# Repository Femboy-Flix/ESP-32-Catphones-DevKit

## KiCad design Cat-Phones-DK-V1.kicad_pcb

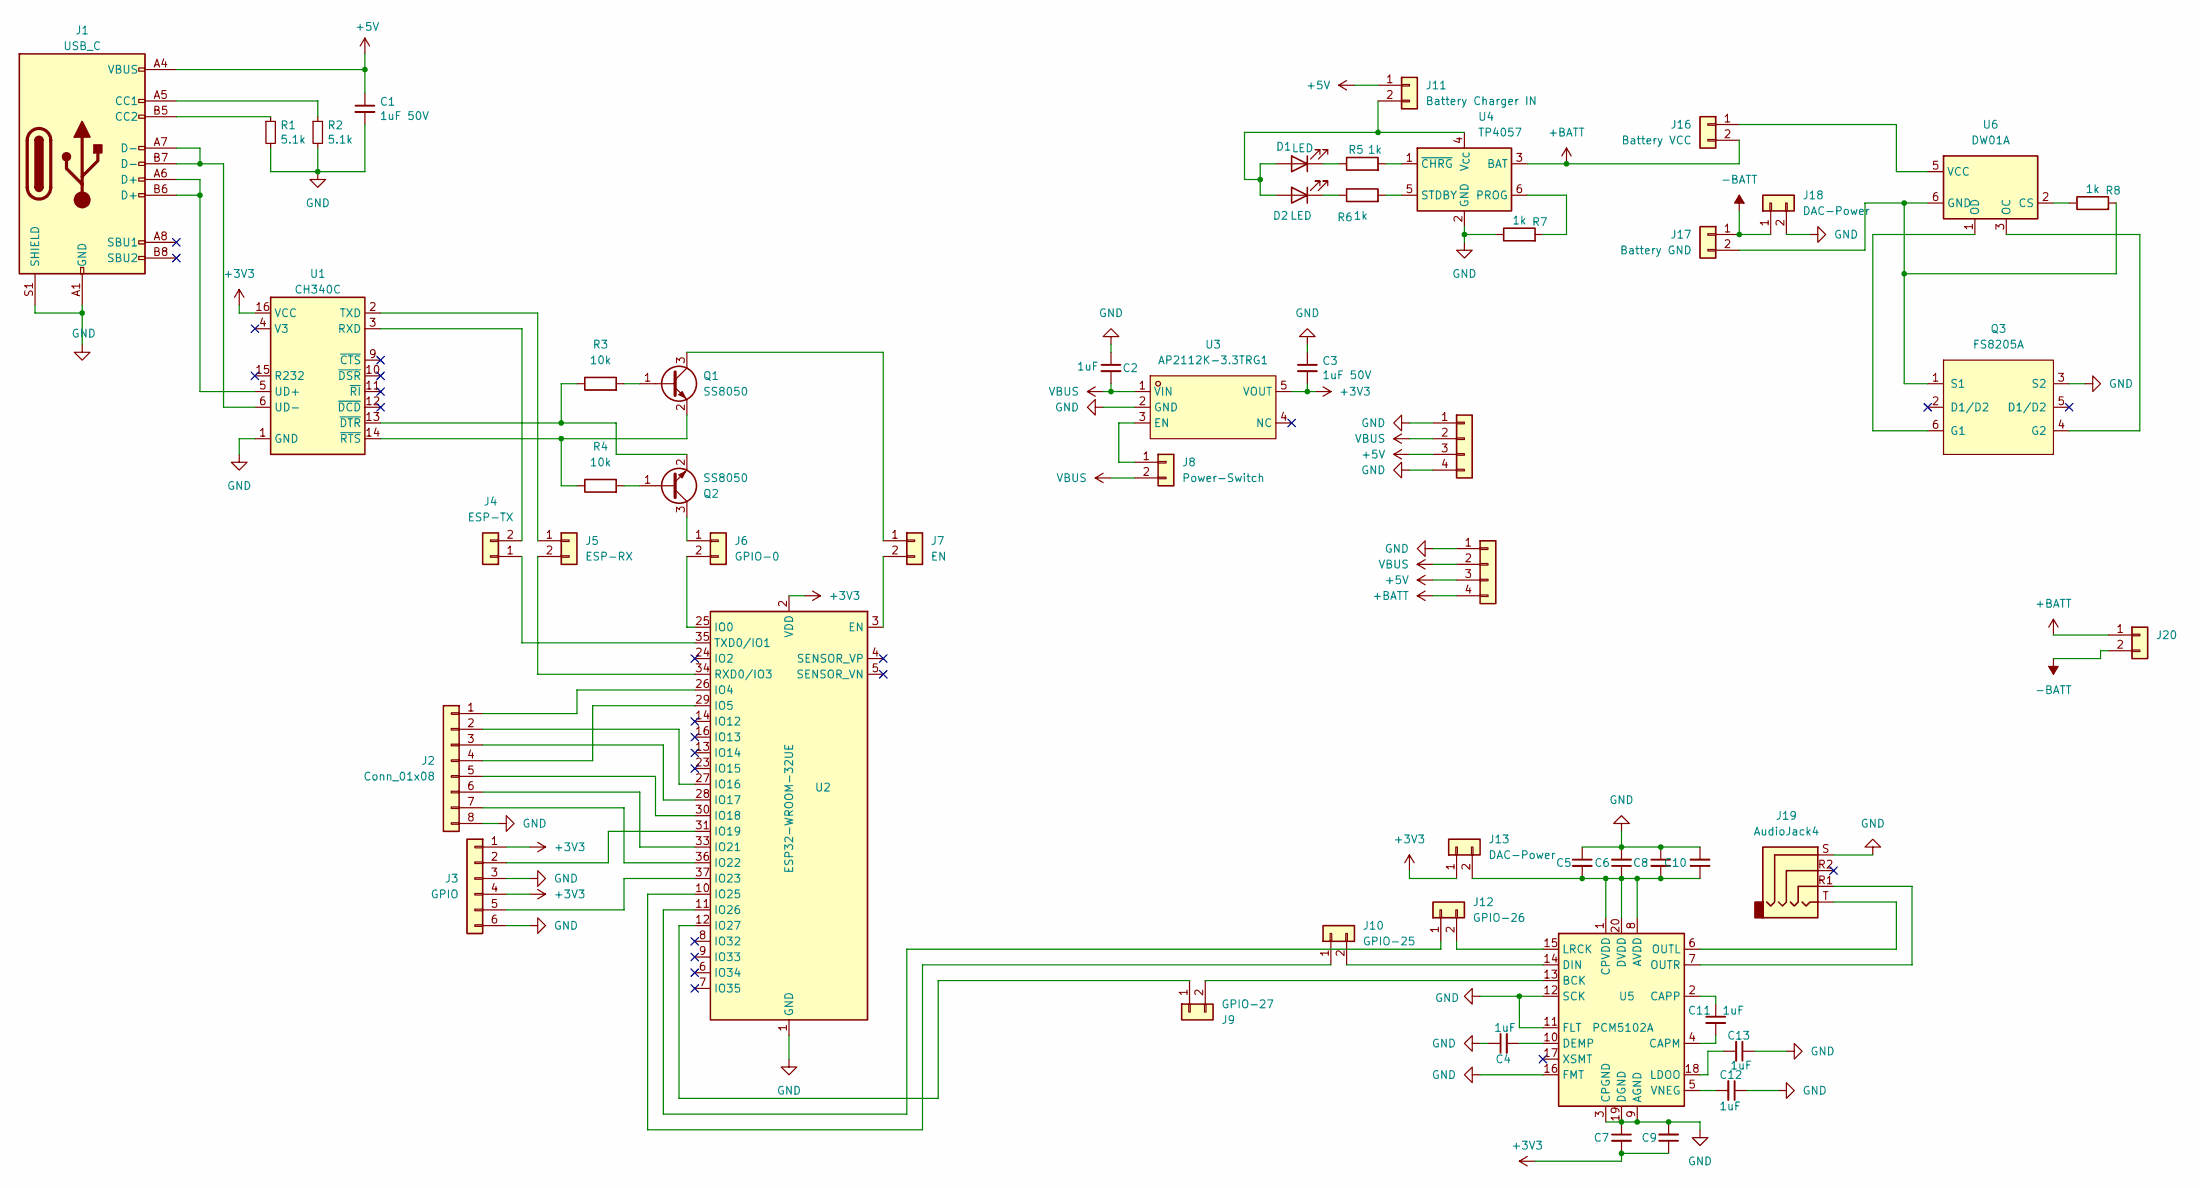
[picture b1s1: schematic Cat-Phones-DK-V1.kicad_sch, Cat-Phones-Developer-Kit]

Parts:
C1, C3, C5, C6, C7, C8, C9, C10: 1uF 50V; C_0805_2012Metric_Pad1.18x1.45mm_HandSolder; Part Number CL10A105KB8NNNC; LCSC CL10A105KB8NNNC
C2, C4, C11, C12, C13: 1uF; C_0805_2012Metric_Pad1.18x1.45mm_HandSolder; Part Number CL10A105KB8NNNC; LCSC CL10A105KB8NNNC
D1, D2: LED; LED_0805_2012Metric
J1: USB_C; USB_C_Receptacle_GCT_USB4105-xx-A_16P_TopMnt_Horizontal; Part Number 2137160001; LCSC C165948
J2: Conn_01x08; PinHeader_1x08_P2.54mm_Vertical
J3: GPIO; PinHeader_1x06_P2.54mm_Vertical
J4: ESP-TX; PinSocket_1x02_P2.54mm_Vertical
J5: ESP-RX; PinSocket_1x02_P2.54mm_Vertical
J6: GPIO-0; PinSocket_1x02_P2.54mm_Vertical
J7: EN; PinSocket_1x02_P2.54mm_Vertical
J8: Power-Switch; PinSocket_1x02_P2.54mm_Vertical
J9: GPIO-27; PinSocket_1x02_P2.54mm_Vertical
J10: GPIO-25; PinSocket_1x02_P2.54mm_Vertical
J11: Battery Charger IN; PinSocket_1x02_P2.54mm_Vertical
J12: GPIO-26; PinSocket_1x02_P2.54mm_Vertical
J13, J18: DAC-Power; PinSocket_1x02_P2.54mm_Vertical
J14, J15: Conn_01x04; PinSocket_1x04_P2.54mm_Vertical
J16: Battery VCC; PinSocket_1x02_P2.54mm_Vertical
J17: Battery GND; PinSocket_1x02_P2.54mm_Vertical
J19: AudioJack4; Jack_3.5mm_PJ320D_Horizontal
J20: Conn_01x02; PinSocket_1x02_P2.00mm_Vertical
Q1, Q2: SS8050; SOT-23
Q3: FS8205A; SOP65P640X120-8N
R1, R2: 5.1k; R_0805_2012Metric_Pad1.20x1.40mm_HandSolder; Part Number 0603WAF5101T5E; LCSC 0603WAF5101T5E
R3, R4: 10k; R_0805_2012Metric_Pad1.20x1.40mm_HandSolder
R5, R6, R7, R8: 1k; R_0805_2012Metric_Pad1.20x1.40mm_HandSolder
U1: CH340C; SOIC-16_3.9x9.9mm_P1.27mm; LCSC C84681
U2: ESP32-WROOM-32UE
U3: AP2112K-3.3TRG1; SOT-23-5; LCSC Part C51118
U4: TP4057; TSOT-23-6
U5: PCM5102A; TSSOP-20_4.4x6.5mm_P0.65mm
U6: DW01A; SOT-23-6

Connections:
+3V3: C3.2, C7.2, C9.1, J3.1, J3.4, J13.1, U1.16 (VCC), U2.2 (VDD), U3.5 (VOUT)
+5V: C1.1, J1.A4 (VBUS), J1.A9 (VBUS), J1.B4 (VBUS), J1.B9 (VBUS), J11.1, J14.3, J15.3
+BATT: J15.4, J16.2, J20.1, U4.3 (BAT)
-BATT: J17.1, J18.1, J20.2
GND: C1.2, C2.1, C3.1, C4.1, C5.1, C6.2, C7.1, C8.1, C9.2, C10.2, C12.1, C13.1, J1.A1 (GND), J1.A12 (GND), J1.B1 (GND), J1.B12 (GND), J1.S1 (SHIELD), J2.8, J3.3, J3.6, J14.1, J14.4, J15.1, J18.2, J19.S, Q3.3 (S2), R1.2, R2.2, R7.1, U1.1 (GND), U2.1 (GND), U2.15 (GND), U2.38 (GND), U2.39 (GND), U3.2 (GND), U4.2 (GND), U5.3 (CPGND), U5.9 (AGND), U5.11 (FLT), U5.12 (SCK), U5.16 (FMT), U5.19 (DGND)
unnamed: D1.2 (A), D2.2 (A), J11.2, U4.4 (V_{CC})
unnamed: D1.1 (K), R5.1
unnamed: D2.1 (K), R6.1
unnamed: J1.A5 (CC1), R2.1
unnamed: J1.B5 (CC2), R1.1
unnamed: J2.1, U2.26 (IO4)
unnamed: J2.2, U2.27 (IO16)
unnamed: J2.3, U2.28 (IO17)
unnamed: J2.4, U2.29 (IO5)
unnamed: J2.5, U2.30 (IO18)
unnamed: J2.6, U2.33 (IO21)
unnamed: J2.7, U2.36 (IO22)
unnamed: J3.2, U2.31 (IO19)
unnamed: J3.5, U2.37 (IO23)
unnamed: J4.1, U2.35 (TXD0/IO1)
unnamed: J4.2, U1.3 (RXD)
unnamed: J5.1, U1.2 (TXD)
unnamed: J5.2, U2.34 (RXD0/IO3)
unnamed: J6.1, Q2.3 (C)
unnamed: J6.2, U2.25 (IO0)
unnamed: J7.1, Q1.3 (C)
unnamed: J7.2, U2.3 (EN)
unnamed: J8.1, U3.3 (EN)
unnamed: J9.1, U2.12 (IO27)
unnamed: J9.2, U5.13 (BCK)
unnamed: J10.1, U2.10 (IO25)
unnamed: J10.2, U5.14 (DIN)
unnamed: J12.1, U2.11 (IO26)
unnamed: J12.2, U5.15 (LRCK)
unnamed: C5.2, C6.1, C8.2, C10.1, J13.2, U5.1 (CPVDD), U5.8 (AVDD), U5.20 (DVDD)
unnamed: J16.1, U6.5 (VCC)
unnamed: J17.2, Q3.1 (S1), R8.2, U6.6 (GND)
unnamed: Q1.1 (B), R3.2
unnamed: Q1.2 (E), R4.1, U1.14 (~RTS)
unnamed: Q2.1 (B), R4.2
unnamed: Q2.2 (E), R3.1, U1.13 (~DTR)
unnamed: Q3.6 (G1), U6.1 (OD)
unnamed: Q3.4 (G2), U6.3 (OC)
unnamed: J1.A6 (D+), J1.B6 (D+), U1.5 (UD+)
unnamed: J1.A7 (D-), J1.B7 (D-), U1.6 (UD-)
unnamed: R7.2, U4.6 (PROG)
unnamed: R6.2, U4.5 (STDBY)
unnamed: R5.2, U4.1 (~CHRG)
unnamed: C11.2, U5.4 (CAPM)
unnamed: C11.1, U5.2 (CAPP)
unnamed: C4.2, U5.10 (DEMP)
unnamed: C13.2, U5.18 (LDOO)
unnamed: J19.T, U5.6 (OUTL)
unnamed: J19.R1, U5.7 (OUTR)
unnamed: C12.2, U5.5 (VNEG)
unnamed: R8.1, U6.2 (CS)
VBUS: C2.2, J8.2, J14.2, J15.2, U3.1 (VIN)

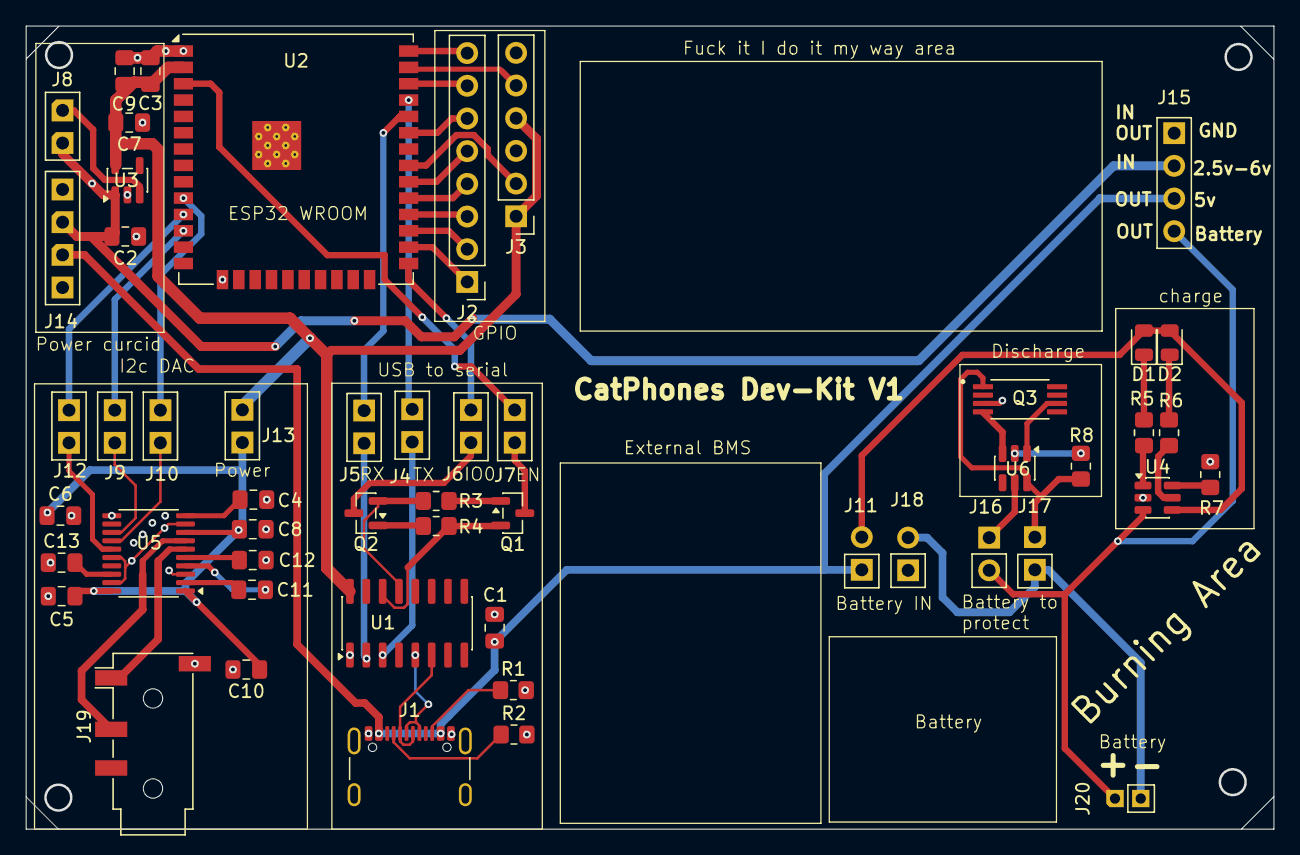
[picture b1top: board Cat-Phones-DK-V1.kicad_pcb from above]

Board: 2 copper layers, 97.0 x 62.4 mm, 52 parts (0 on the bottom side), 57 nets.

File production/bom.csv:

Designator,Footprint,Quantity,Value,LCSC Part #
"C1, C10, C3, C5, C6, C7, C8, C9",0805,8,1uF  50V,CL10A105KB8NNNC
"C11, C12, C13, C2, C4",0805,5,1uF,CL10A105KB8NNNC
"D1, D2",0805,2,LED,
J1,USB_C_Receptacle_GCT_USB4105-xx-A_16P_TopMnt_Horizontal,1,USB_C,C165948
J10,PinSocket_1x02_P2.54mm_Vertical,1,GPIO-25,
J11,PinSocket_1x02_P2.54mm_Vertical,1,Battery Charger IN,
J12,PinSocket_1x02_P2.54mm_Vertical,1,GPIO-26,
"J13, J18",PinSocket_1x02_P2.54mm_Vertical,2,DAC-Power,
"J14, J15",PinSocket_1x04_P2.54mm_Vertical,2,Conn_01x04,
J16,PinSocket_1x02_P2.54mm_Vertical,1,Battery VCC,
J17,PinSocket_1x02_P2.54mm_Vertical,1,Battery GND,
J19,Jack_3.5mm_PJ320D_Horizontal,1,AudioJack4,
J2,PinHeader_1x08_P2.54mm_Vertical,1,Conn_01x08,
J20,PinSocket_1x02_P2.00mm_Vertical,1,Conn_01x02,
J3,PinHeader_1x06_P2.54mm_Vertical,1,GPIO,
J4,PinSocket_1x02_P2.54mm_Vertical,1,ESP-TX,
J5,PinSocket_1x02_P2.54mm_Vertical,1,ESP-RX,
J6,PinSocket_1x02_P2.54mm_Vertical,1,GPIO-0,
J7,PinSocket_1x02_P2.54mm_Vertical,1,EN,
J8,PinSocket_1x02_P2.54mm_Vertical,1,Power-Switch,
J9,PinSocket_1x02_P2.54mm_Vertical,1,GPIO-27,
"Q1, Q2",SOT-23,2,SS8050,
Q3,SOP65P640X120-8N,1,FS8205A,
"R1, R2",0805,2,5.1k,0603WAF5101T5E
"R3, R4",0805,2,10k,
"R5, R6, R7, R8",0805,4,1k,
U1,SOIC-16_3.9x9.9mm_P1.27mm,1,CH340C,C84681
U2,ESP32-WROOM-32UE,1,ESP32-WROOM-32UE,
U3,SOT-23-5,1,AP2112K-3.3TRG1,C51118
U4,TSOT-23-6,1,TP4057,
U5,TSSOP-20_4.4x6.5mm_P0.65mm,1,PCM5102A,
U6,SOT-23-6,1,DW01A,
